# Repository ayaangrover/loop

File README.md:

<div align="center">

# Loop: Compact MP3 Player

</div>

Loop is a compact MP3 player that's designed to be simple and portable.

## Features

- Can play and store up to 10,000 MP3 files from a microSD card
- 3.5mm TRRS headphone jack
- (Optional) speaker support
- Dual playback support(both headphones and speaker)
- USB-C charging
- 8-10 hours of battery life
- Physical buttons for control
- Custom 3D-printed case (magnet and screw versions)

## Parts List

| Component           | Source                                | Price   |
|---------------------|----------------------------------------|---------|
| DFPlayer            | Amazon                                 | $10.00  |
| TP4056              | AliExpress                             | $2.00   |
| M2 Screws           | Aliexpress                             | $2.00   |
| M2 Heatset Inserts  | Aliexpress                             | $2.00   |
| LiPo Battery        | Amazon (900mAh)                        | $8.00   |
| Audio Jack          | LCSC                                   | $11.50  |
| Buttons (x3)        | LCSC                                   | $0.60   |
| Resistors           | LCSC                                   | $1.41   |
| Speaker (x2)        | Aliexpress                             | $1.90   |
| PCB                 | JLCPCB                                 | $31.00  |
| Case                | Printed via Hack Club #printing-legion | Free    |
| MicroSD Card        | Aliexpress                             | $3.00   |
| **Total**           | —                                      | **$73.41** |

## Enclosure

Designed in Fusion 360. Available in ```./case```.

## Firmware

No firmware needed! DFPlayer handles all the playing.

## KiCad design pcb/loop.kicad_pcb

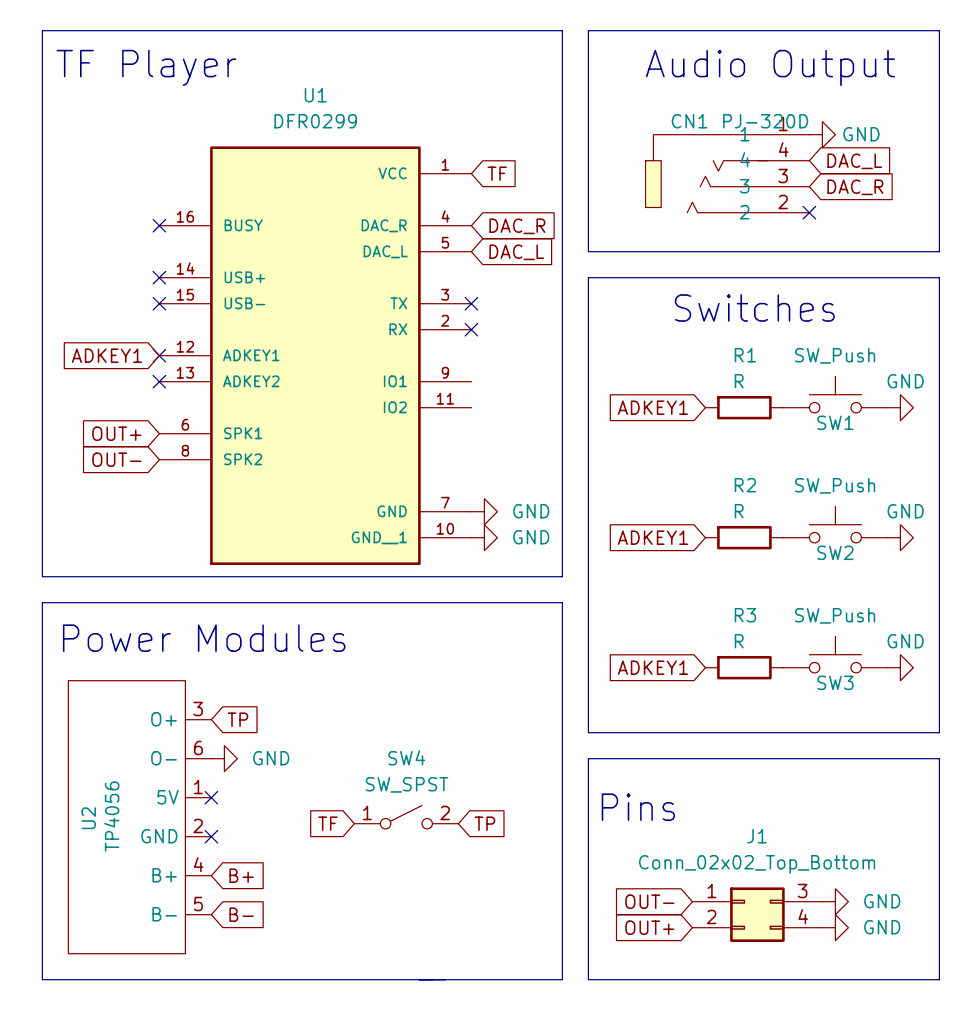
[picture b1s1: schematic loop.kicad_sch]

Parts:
CN1: PJ-320D; AUDIO-SMD_PJ-320D; LCSC Part C431535
J1: Conn_02x02_Top_Bottom; PinHeader_1x04_P2.00mm_Vertical
R1, R2, R3: R; R_Axial_DIN0207_L6.3mm_D2.5mm_P7.62mm_Horizontal
SW1, SW2, SW3: SW_Push; SW_PUSH_6mm
SW4: SW_SPST; SW-TH_SK12D07VG5
U1: DFR0299; MODULE_DFR0299
U2: TP4056

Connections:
ADKEY1: R1.2, R2.2, R3.2, U1.12 (ADKEY1)
B+: U2.4 (B+)
B-: U2.5 (B-)
DAC_L: CN1.4, U1.5 (DAC_L)
DAC_R: CN1.3, U1.4 (DAC_R)
GND: CN1.1, J1.3, J1.4, SW1.2, SW2.2, SW3.2, U1.7 (GND), U1.10 (GND__1), U2.6 (O-)
unnamed: R1.1, SW1.1
unnamed: R2.1, SW2.1
unnamed: R3.1, SW3.1
OUT+: J1.2, U1.6 (SPK1)
OUT-: J1.1, U1.8 (SPK2)
TF: SW4.1 (A), U1.1 (VCC)
TP: SW4.2 (B), U2.3 (O+)

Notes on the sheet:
Switches
Audio Output
Power Modules
TF Player
Pins

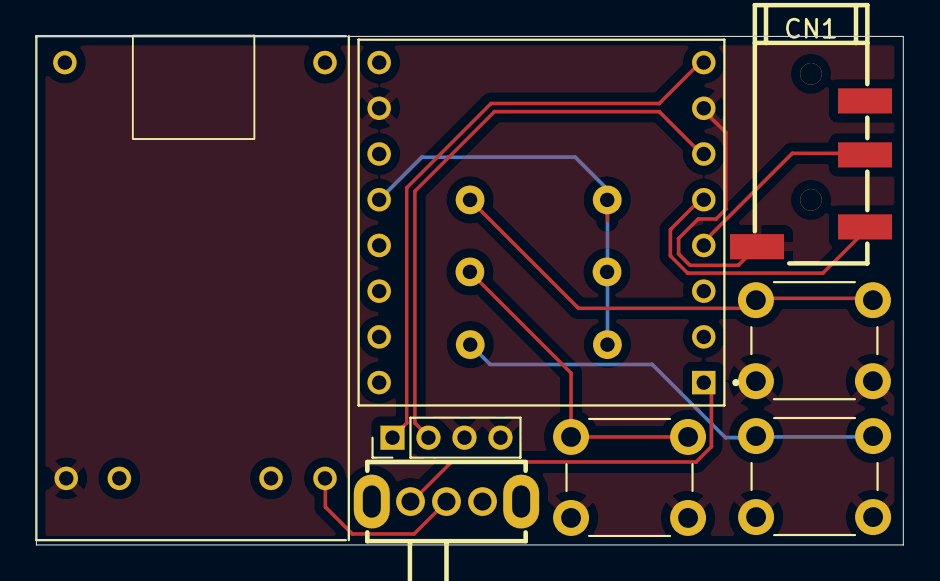
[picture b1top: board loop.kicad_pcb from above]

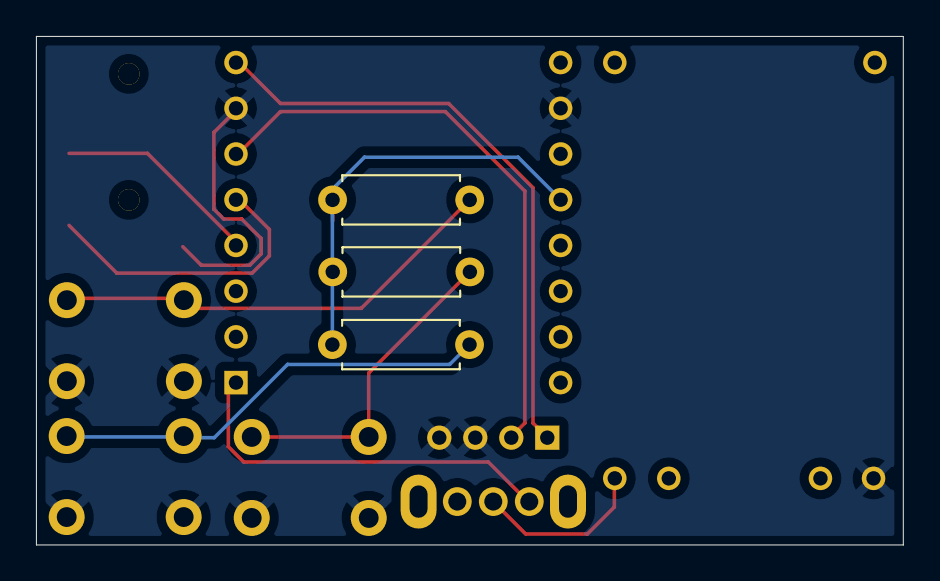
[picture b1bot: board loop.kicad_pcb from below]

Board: 2 copper layers, 48.2 x 28.2 mm, 11 parts (3 on the bottom side), 11 nets.

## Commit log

2025-07-31 Add PCB and Case
2025-07-31 update info
2025-07-31 update case
2025-07-31 update data
